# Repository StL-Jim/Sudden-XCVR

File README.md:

# Sudden-XCVR

These are the EagleCAD schematics and board files for the QRP Transceiver designed and built by Pete Julino N6QW called the Sudden Transceiver.  

I am very new to building a truly scratch built rig, so any suggestions, comments, corrections are greatly appreciated.

Read about the Sudden Scratch Built SSB Transceiver - http://www.n6qw.com/Sudden.html

I use a style of construction coined by Chuck Adams K7QO called 'Muppet Style', you can learn about this style of building from Chuck's YouTube channel

* https://www.youtube.com/watch?v=O6AmT1trO60

As I progress along I'll be adding PDF of the schematics and boards as well as the EagleCAD parts library I use.

73 - AE0BZ

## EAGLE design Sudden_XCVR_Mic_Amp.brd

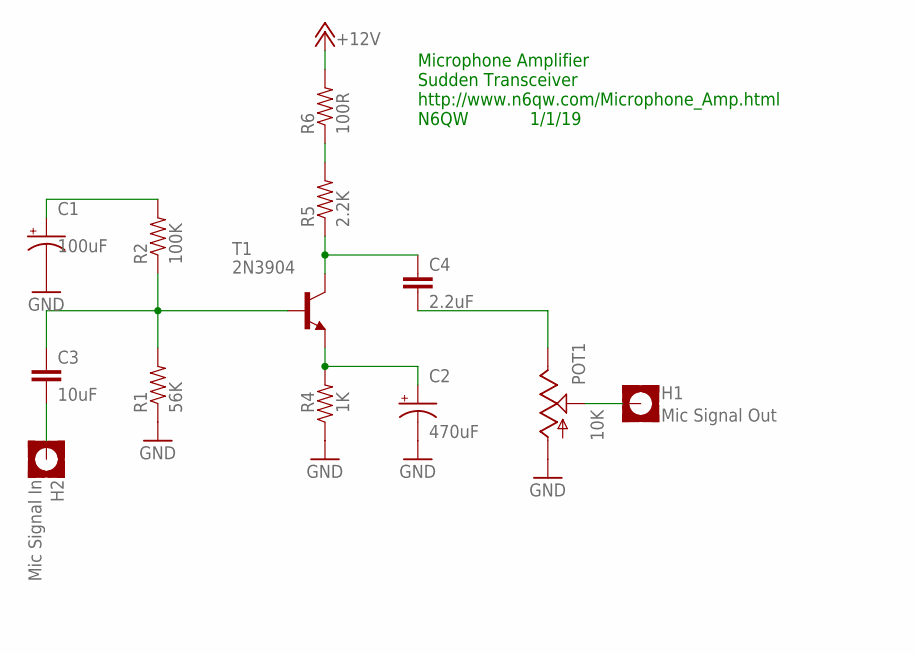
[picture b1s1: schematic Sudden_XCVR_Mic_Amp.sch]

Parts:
C1: 100uF; CAP-POLARIZED
C2: 470uF; CAP-POLARIZED
C3: 10uF; CAP-MEDIUM-MUPPET
C4: 2.2uF; CAP-MEDIUM-MUPPET
H1: Mic Signal Out; PAD-SQUARE
H2: Mic Signal In; PAD-SQUARE
P+1: +12V; POWER-IN-PAD
POT1: 10K; POT-TRIMM-4
R1: 56K; RESITOR-MUPPET
R2: 100K; RESITOR-MUPPET
R4: 1K; RESITOR-MUPPET
R5: 2.2K; RESITOR-MUPPET
R6: 100R; RESITOR-MUPPET
T1: 2N3904; TO92

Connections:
+12V: P+1.VCC, R6.P$2 (2)
GND: C1.2 (-), C2.2 (-), POT1.A, R1.P$1 (1), R4.P$1 (1)
unnamed: C4.1, R5.P$1 (1), T1.1 (C)
unnamed: C2.1 (+), R4.P$2 (2), T1.3 (E)
unnamed: C4.2, POT1.E
unnamed: C3.1, R1.P$2 (2), R2.P$1 (1), T1.2 (B)
unnamed: C1.1 (+), R2.P$2 (2)
unnamed: R5.P$2 (2), R6.P$1 (1)
unnamed: H1.PAD, POT1.S
unnamed: C3.2, H2.PAD

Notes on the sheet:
Microphone Amplifier Sudden Transceiver http://www.n6qw.com/Microphone_Amp.html N6QW 1/1/19

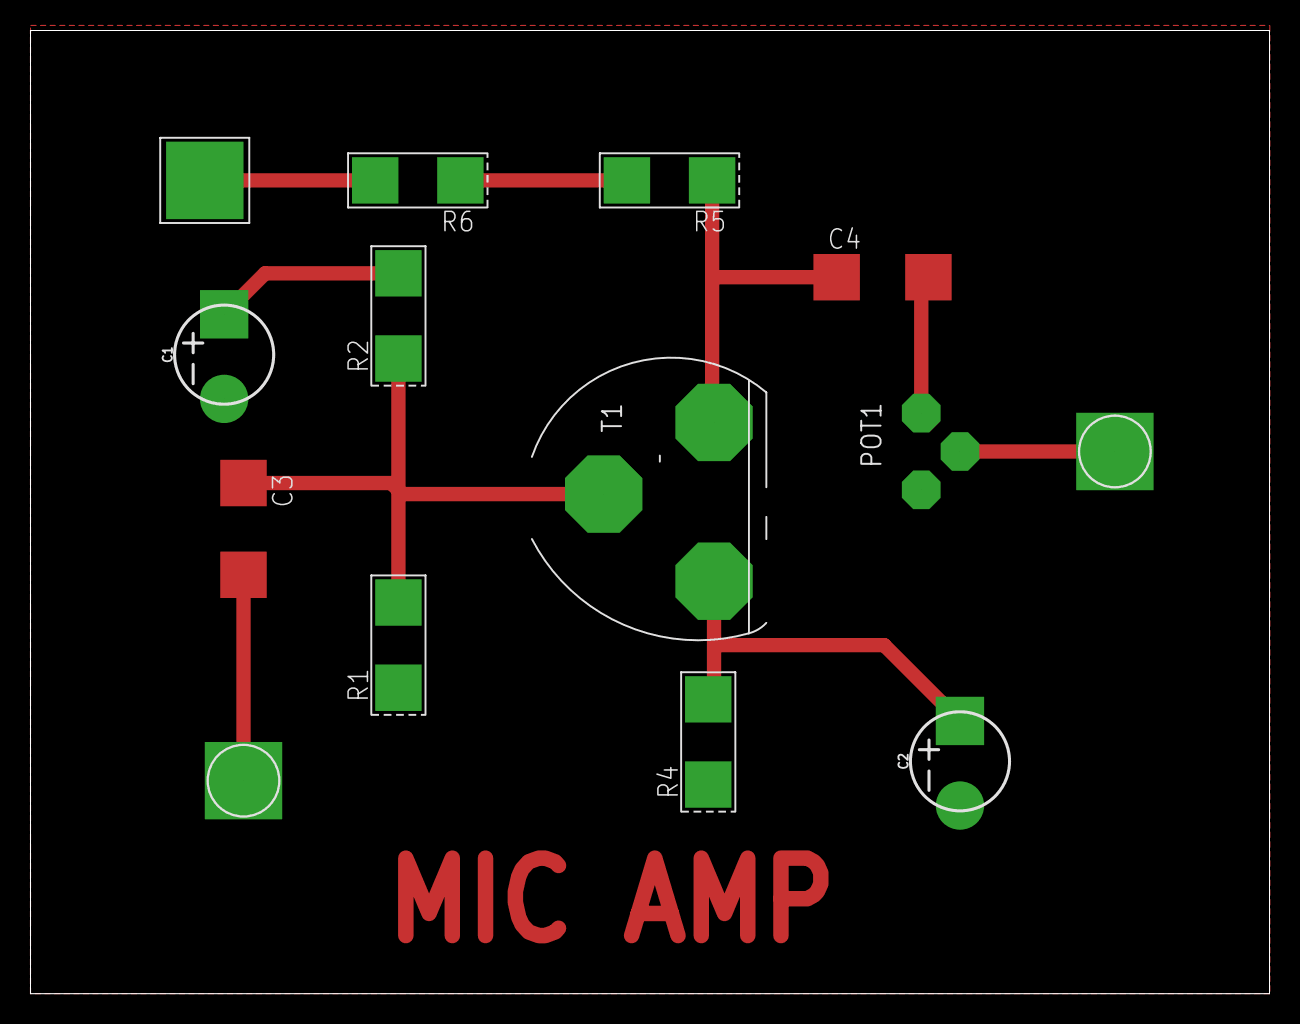
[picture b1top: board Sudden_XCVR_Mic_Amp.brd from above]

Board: 2 copper layers, 81.3 x 63.2 mm, 14 parts (1 on the bottom side), 10 nets.

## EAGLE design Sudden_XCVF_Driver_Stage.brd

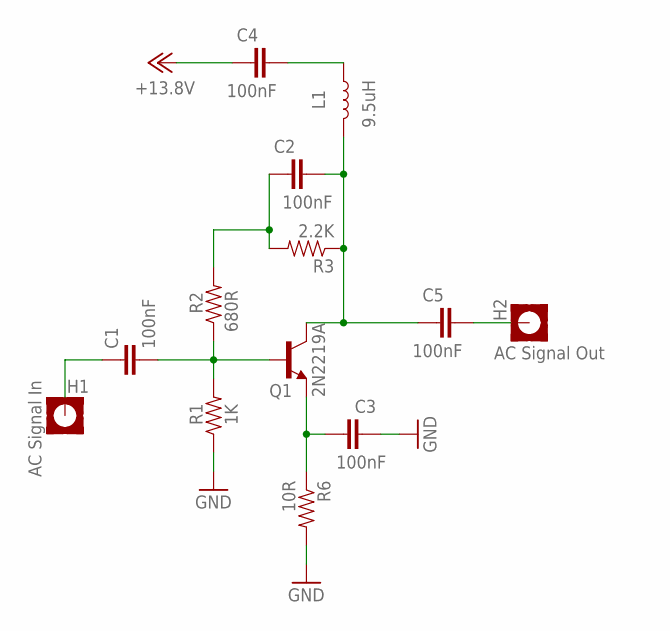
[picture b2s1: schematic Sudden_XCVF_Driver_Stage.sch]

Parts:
C1, C2, C3, C4, C5: 100nF; CAP-MEDIUM-MUPPET
H1: AC Signal In; PAD-SQUARE
H2: AC Signal Out; PAD-SQUARE
L1: 9.5uH; INDUCTOR_2.2UH
P+1: +13.8V; POWER-IN-PAD
Q1: 2N2219A; 2N2222-TO18
R1: 1K; RESITOR-MUPPET
R2: 680R; RESITOR-MUPPET
R3: 2.2K; RESITOR-MUPPET
R6: 10R; RESITOR-MUPPET

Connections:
+12V: C4.1, P+1.VCC
GND: C3.1, R1.P$1 (1), R6.P$2 (2)
unnamed: C1.2, Q1.2 (B), R1.P$2 (2), R2.P$1 (1)
unnamed: C2.2, C5.1, L1.P$2 (2), Q1.3 (C), R3.P$1 (1)
unnamed: C5.2, H2.PAD
unnamed: C2.1, R2.P$2 (2), R3.P$2 (2)
unnamed: C1.1, H1.PAD
unnamed: C4.2, L1.P$1 (1)
unnamed: C3.2, Q1.1 (E), R6.P$1 (1)

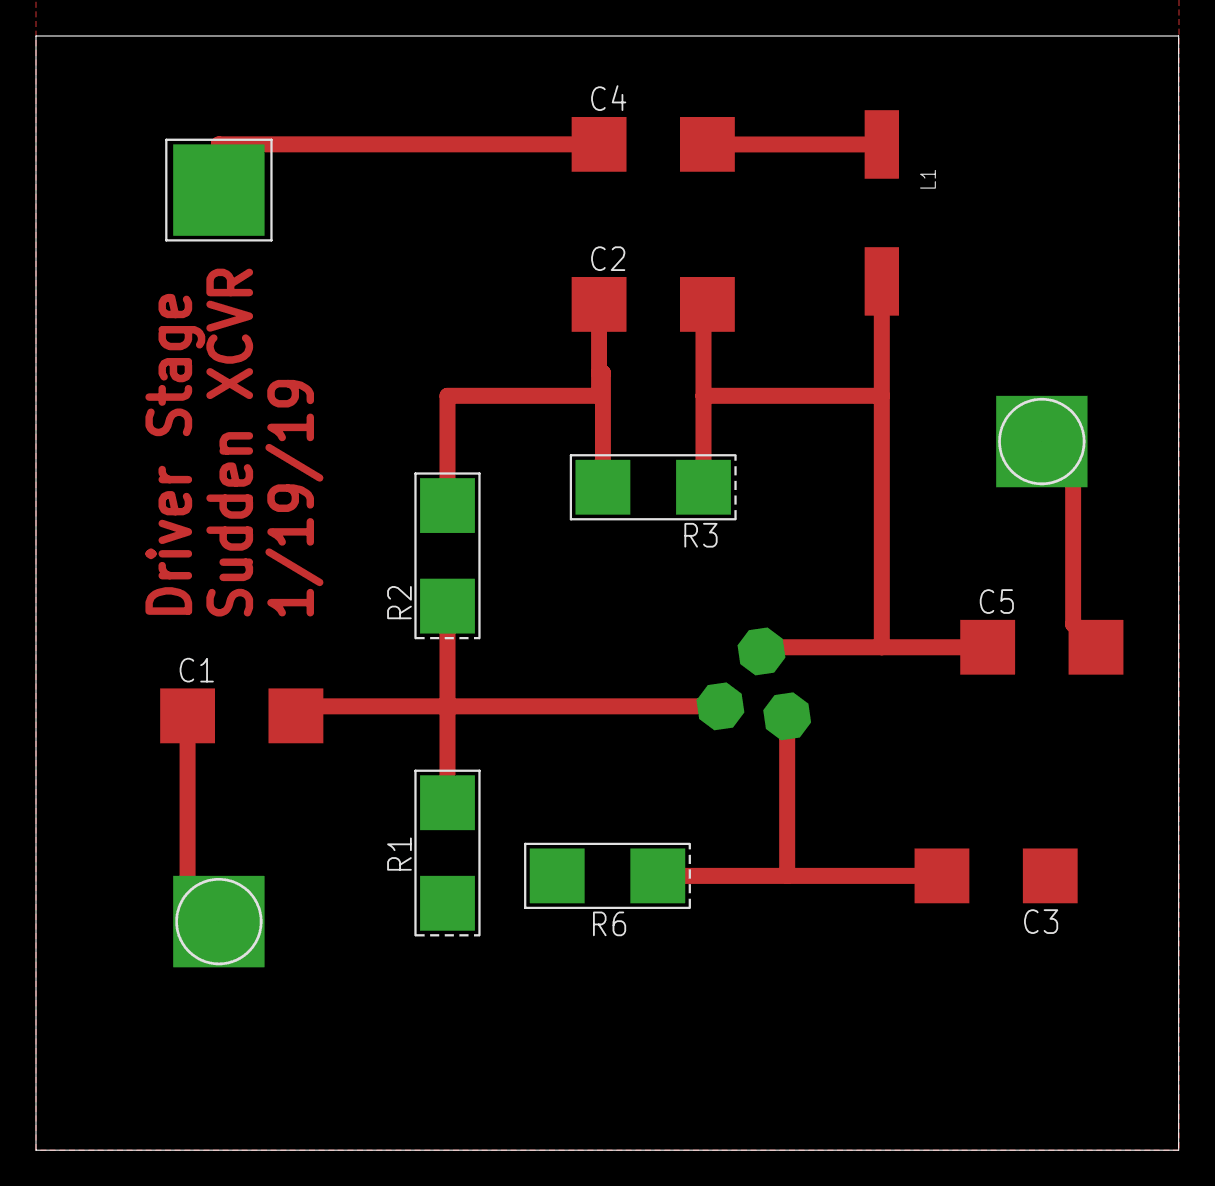
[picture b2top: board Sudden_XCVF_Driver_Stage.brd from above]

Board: 2 copper layers, 63.5 x 61.9 mm, 14 parts (1 on the bottom side), 9 nets.

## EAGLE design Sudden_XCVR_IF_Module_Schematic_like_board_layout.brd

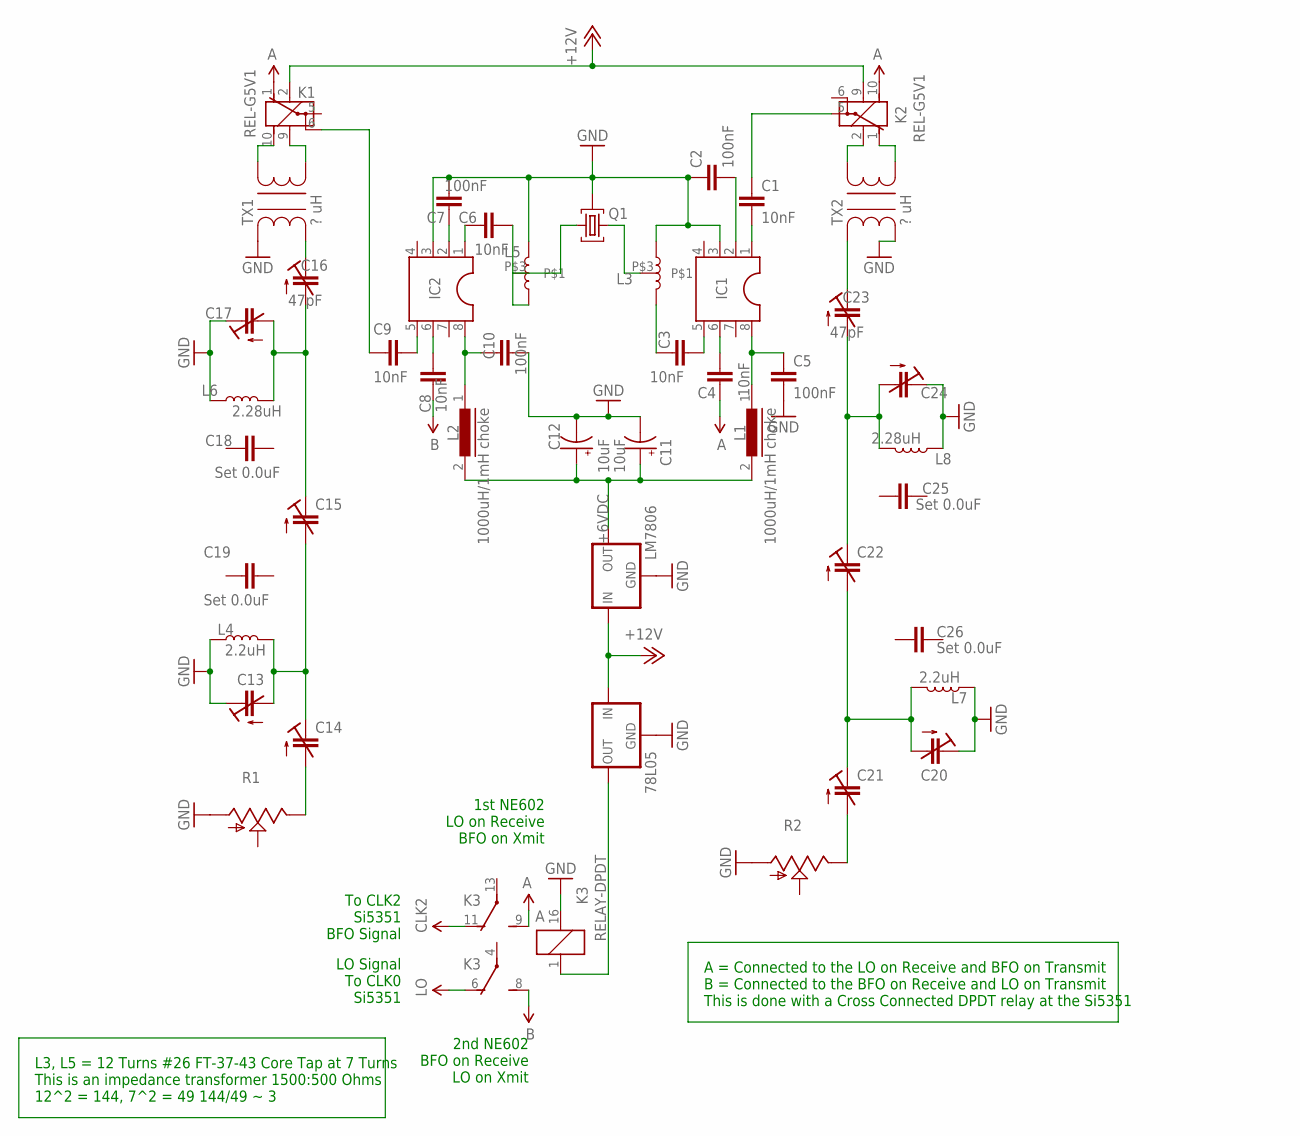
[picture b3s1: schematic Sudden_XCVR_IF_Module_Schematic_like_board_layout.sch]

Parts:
78L05: 78XXL
A, A1, A2: A; POWER-IN-PAD
B: B; POWER-IN-PAD
C1, C3, C4, C6, C8, C9: 10nF; CAP-MEDIUM-MUPPET
C2, C5, C7, C10: 100nF; CAP-MEDIUM-MUPPET
C11, C12: 10uF; CAP-POLARIZED
C13, C14, C15, C17, C20, C21, C22, C24: CAP-TRIMM3008; CAP-TRIMM
C16, C23: 47pF; CAP-TRIMM
C18, C19, C25, C26: Set 0.0uF; CAP-MEDIUM-MUPPET
CLK0: LO; POWER-IN-PAD
CLK1: A; POWER-IN-PAD
CLK2: CLK2; POWER-IN-PAD
IC1, IC2: DUAL-INLINE-8DIL08-2; DIL08
K1, K2: REL-G5V1; G5V1
K3: RELAY-DPDT; G5V-2
L1, L2: 1000uH/1mH choke; MOLDED-CHOKE
L3: INDUCTOR-TAPPED; INDUCTOR_TAPPED
L4, L7: 2.2uH; INDUCTOR_2.2UH
L5: INDUCTOR-TAPPED; INDUCTOR_TAPPED_MIRRORED
L6, L8: 2.28uH; INDUCTOR_2.2UH
LM7806: 78XXL
P+1, P+2: +12V; POWER-IN-PAD
Q1: CRYSTAL-FILTER
R1, R2: POTENTIOMETER-TRIMCT6; POT-TRIMM-4
SUPPLY1: B; POWER-IN-PAD
TX1, TX2: ? uH; TRANSFORMER_TWO_WIRE

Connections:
3.3V: A1.VCC, A2.VCC, B.VCC, C8.1, K1.1 (O), K2.10 (S), K3.8 (S), SUPPLY1.VCC
+6VDC: C11.1 (+), C12.1 (+), L1.2, L2.2, LM7806.OUT
+12V: 78L05.IN, K1.2 (1), K2.9 (2), LM7806.IN, P+1.VCC, P+2.VCC
A: A.VCC, C4.1, CLK0.VCC, CLK1.VCC, K3.6 (O), K3.9 (S)
BFO: CLK2.VCC, K3.11 (O)
GND: 78L05.GND, C2.1, C5.2, C7.1, C10.2, C11.2 (-), C12.2 (-), C13.+ (E), C17.+ (E), C20.+ (E), C24.+ (E), IC1.3, IC2.3, K3.16 (2), L3.P$2 (2), L4.P$1 (1), L5.P$1 (1), L6.P$1 (1), L7.P$1 (1), L8.P$1 (1), LM7806.GND, Q1.3, R1.A, R2.A, TX1.C1B (2), TX2.C1A (1)
unnamed: C5.1, IC1.8, L1.1
unnamed: C4.2, IC1.6
unnamed: C3.2, IC1.5
unnamed: L5.P$3, Q1.1
unnamed: C1.2, IC1.1
unnamed: 78L05.OUT, K3.1
unnamed: C2.2, IC1.2
unnamed: C16.+ (E), TX1.C1A (1)
unnamed: C10.1, IC2.8, L2.1
unnamed: C8.2, IC2.6
unnamed: C9.2, IC2.5
unnamed: C6.2, IC2.1
unnamed: C6.1, L5.P$2 (2)
unnamed: C7.2, IC2.2
unnamed: L3.P$3, Q1.2
unnamed: C3.1, L3.P$1 (1)
unnamed: C1.1, K2.5
unnamed: C9.1, K1.6
unnamed: C15.+ (E), C16.- (A), C17.- (A), L6.P$2 (2)
unnamed: C14.- (A), R1.E
unnamed: C13.- (A), C14.+ (E), C15.- (A), L4.P$2 (2)
unnamed: C23.+ (E), TX2.C1B (2)
unnamed: C22.+ (E), C23.- (A), C24.- (A), L8.P$2 (2)
unnamed: C20.- (A), C21.+ (E), C22.- (A), L7.P$2 (2)
unnamed: C21.- (A), R2.E
unnamed: K1.9 (2), TX1.C2A (5)
unnamed: K1.10 (S), TX1.C2B (6)
unnamed: K2.2 (1), TX2.C2B (6)
unnamed: K2.1 (O), TX2.C2A (5)

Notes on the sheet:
L3, L5 = 12 Turns #26 FT-37-43 Core Tap at 7 Turns This is an impedance transformer 1500:500 Ohms 12^2 = 144, 7^2 = 49 144/49 ~ 3
A = Connected to the LO on Receive and BFO on Transmit B = Connected to the BFO on Receive and LO on Transmit This is done with a Cross Connected DPDT relay at the Si5351
1st NE602 LO on Receive BFO on Xmit
2nd NE602 BFO on Receive LO on Xmit
LO Signal To CLK0 Si5351
To CLK2 Si5351 BFO Signal

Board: 2 copper layers, 56 parts (0 on the bottom side), 35 nets, no tracks yet.

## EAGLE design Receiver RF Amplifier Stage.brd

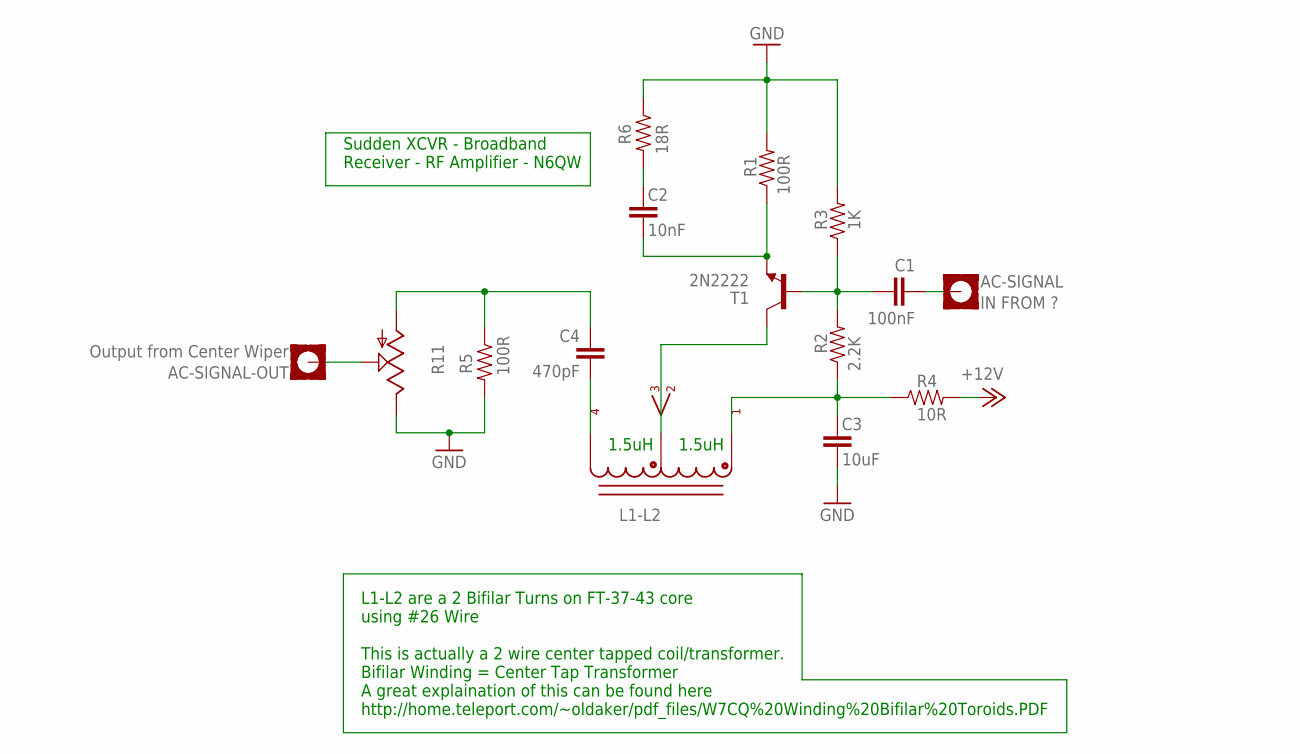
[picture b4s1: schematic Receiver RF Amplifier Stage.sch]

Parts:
AC-SIGNAL: IN FROM ?; PAD-SQUARE
AC-SIGNAL-OUT: Output from Center Wiper; PAD-SQUARE
C1: 100nF; CAP-MEDIUM-MUPPET
C2: 10nF; CAP-MEDIUM-MUPPET
C3: 10uF; CAP-MEDIUM-MUPPET
C4: 470pF; CAP-MEDIUM-MUPPET
L1-L2: T37-43_BIFILAR_TORIODBIFILAR-COIL/TRANSFORMER; T37-43_BIFILAR_TOROID
P+1: +12V; POWER-IN-PAD
R1, R5: 100R; RESITOR-MUPPET
R2: 2.2K; RESITOR-MUPPET
R3: 1K; RESITOR-MUPPET
R4: 10R; RESITOR-MUPPET
R6: 18R; RESITOR-MUPPET
R11: POTENTIOMETER-TRIMCT6; POT-TRIMM-4
T1: 2N2222; 2N2222-TO18

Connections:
+12V: P+1.VCC, R4.P$2 (2)
GND: C3.1, R1.P$2 (2), R3.P$2 (2), R5.P$2 (2), R6.P$1 (1), R11.E
unnamed: C1.1, R2.P$2 (2), R3.P$1 (1), T1.2 (B)
unnamed: AC-SIGNAL-OUT.PAD, R11.S
unnamed: C2.2, R6.P$2 (2)
unnamed: L1-L2.C2A, T1.3 (C)
unnamed: C4.1, L1-L2.C3A
unnamed: C3.2, L1-L2.C1A, R2.P$1 (1), R4.P$1 (1)
unnamed: C4.2, R5.P$1 (1), R11.A
unnamed: AC-SIGNAL.PAD, C1.2
unnamed: C2.1, R1.P$1 (1), T1.1 (E)

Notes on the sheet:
Sudden XCVR - Broadband Receiver - RF Amplifier - N6QW
L1-L2 are a 2 Bifilar Turns on FT-37-43 core using #26 Wire This is actually a 2 wire center tapped coil/transformer. Bifilar Winding = Center Tap Transformer A great explaination of this can be found here http://home.teleport.com/~oldaker/pdf_files/W7CQ%20Winding%20Bifilar%20Toroids.PDF
1.5uH

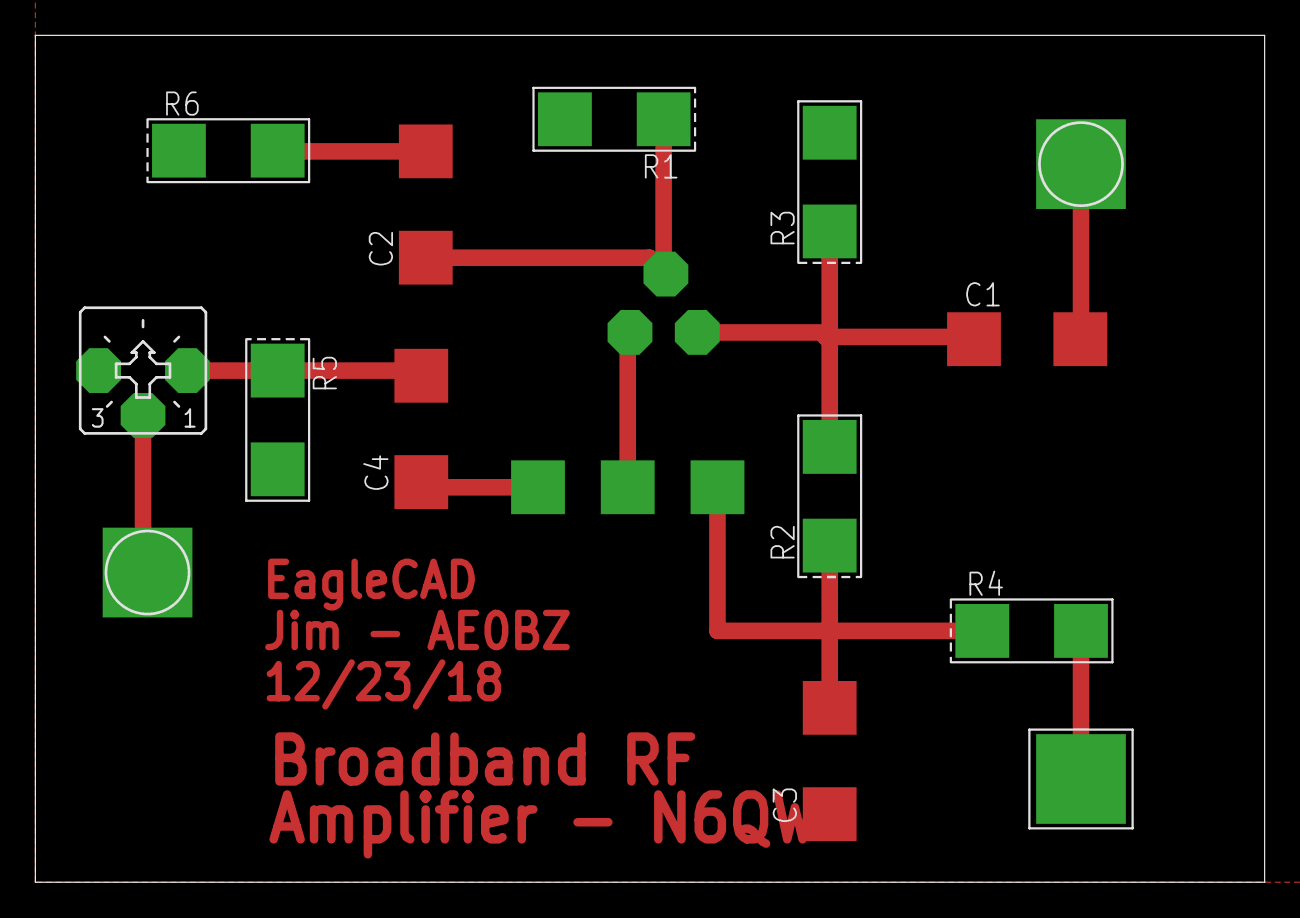
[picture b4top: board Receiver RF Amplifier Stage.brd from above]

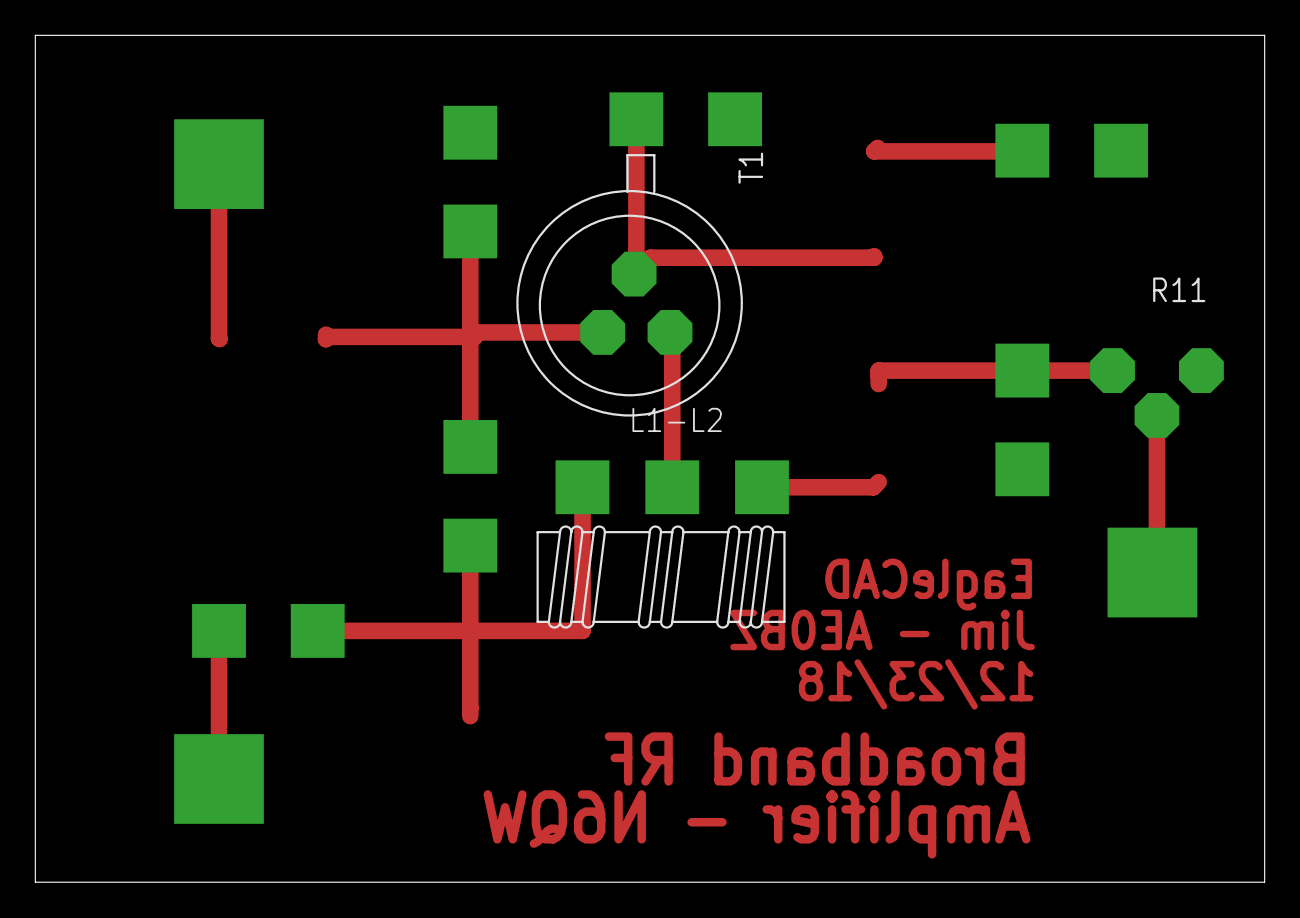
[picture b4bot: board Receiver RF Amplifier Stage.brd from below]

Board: 2 copper layers, 69.6 x 47.9 mm, 16 parts (2 on the bottom side), 11 nets.

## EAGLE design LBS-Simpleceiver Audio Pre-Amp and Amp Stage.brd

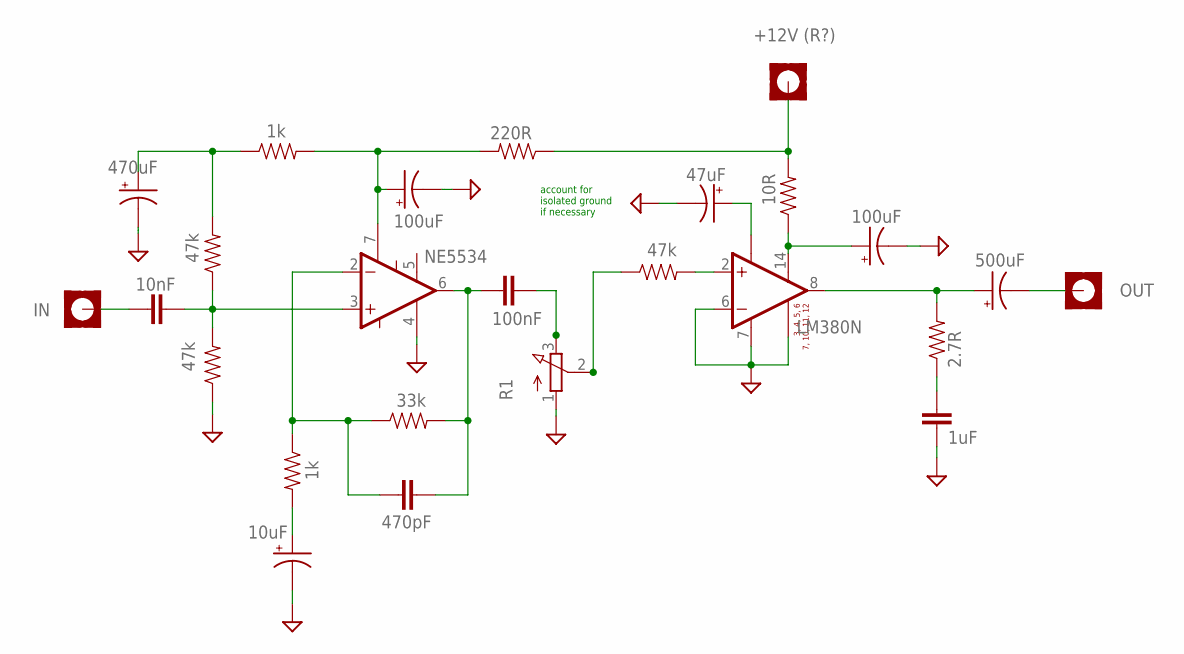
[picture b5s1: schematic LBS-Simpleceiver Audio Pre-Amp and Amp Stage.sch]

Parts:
C1: 470uF; CAP-POLARIZED
C2, C6: 100uF; CAP-POLARIZED
C3: 500uF; CAP-POLARIZED
C4: 47uF; CAP-POLARIZED
C5: 10uF; CAP-POLARIZED
C7: 10nF; CAP-MEDIUM-MUPPET
C8: 100nF; CAP-MEDIUM-MUPPET
C9: 1uF; CAP-MEDIUM-MUPPET
C10: 470pF; CAP-MEDIUM-MUPPET
H1: IN; PAD-SQUARE
H2: OUT; PAD-SQUARE
H3: +12V (R?); PAD-SQUARE
IC1: NE5534; DIL08
R1: POTENTIOMETER
R2, R3: 47k; RESITOR-MUPPET
R4: 1k; RESITOR-MUPPET
R5: 33k; RESITOR-MUPPET
R8: 220R; RESITOR-MUPPET
R9: 2.7R; RESITOR-MUPPET
U1: LM380N; DIL14
U$4: 1k; RESITOR-MUPPET
U$6: 47k; RESITOR-MUPPET
U$7: 10R; RESITOR-MUPPET

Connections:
GND: C1.2 (-), C2.2 (-), C4.2 (-), C5.2 (-), C6.2 (-), C9.2, IC1.4 (VCC-GND), R1.1 (A), R3.P$1 (1), U1.3 (GND), U1.4 (GND), U1.5 (GND), U1.6 (-IN), U1.7 (GND1), U1.10 (GND), U1.11 (GND), U1.12 (GND)
unnamed: C7.1, H1.PAD
unnamed: C7.2, IC1.3 (+IN), R2.P$1 (1), R3.P$2 (2)
unnamed: C1.1 (+), R2.P$2 (2), R4.P$1 (1)
unnamed: C6.1 (+), IC1.7 (VCC+), R4.P$2 (2), R8.P$2 (2)
unnamed: C8.2, C10.1, IC1.6 (OUT), R5.P$2 (2)
unnamed: C10.2, IC1.2 (-IN), R5.P$1 (1), U$4.P$1 (1)
unnamed: C5.1 (+), U$4.P$2 (2)
unnamed: C8.1, R1.3 (E)
unnamed: R1.2 (S), U$6.P$1 (1)
unnamed: U1.2 (+IN), U$6.P$2 (2)
unnamed: C2.1 (+), U1.14 (V-SIG), U$7.P$1 (1)
unnamed: H3.PAD, R8.P$1 (1), U$7.P$2 (2)
unnamed: C3.1 (+), R9.P$2 (2), U1.8 (GAIN)
unnamed: C9.1, R9.P$1 (1)
unnamed: C4.1 (+), U1.1 (BYPASS)
unnamed: C3.2 (-), H2.PAD

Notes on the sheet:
account for isolated ground if necessary

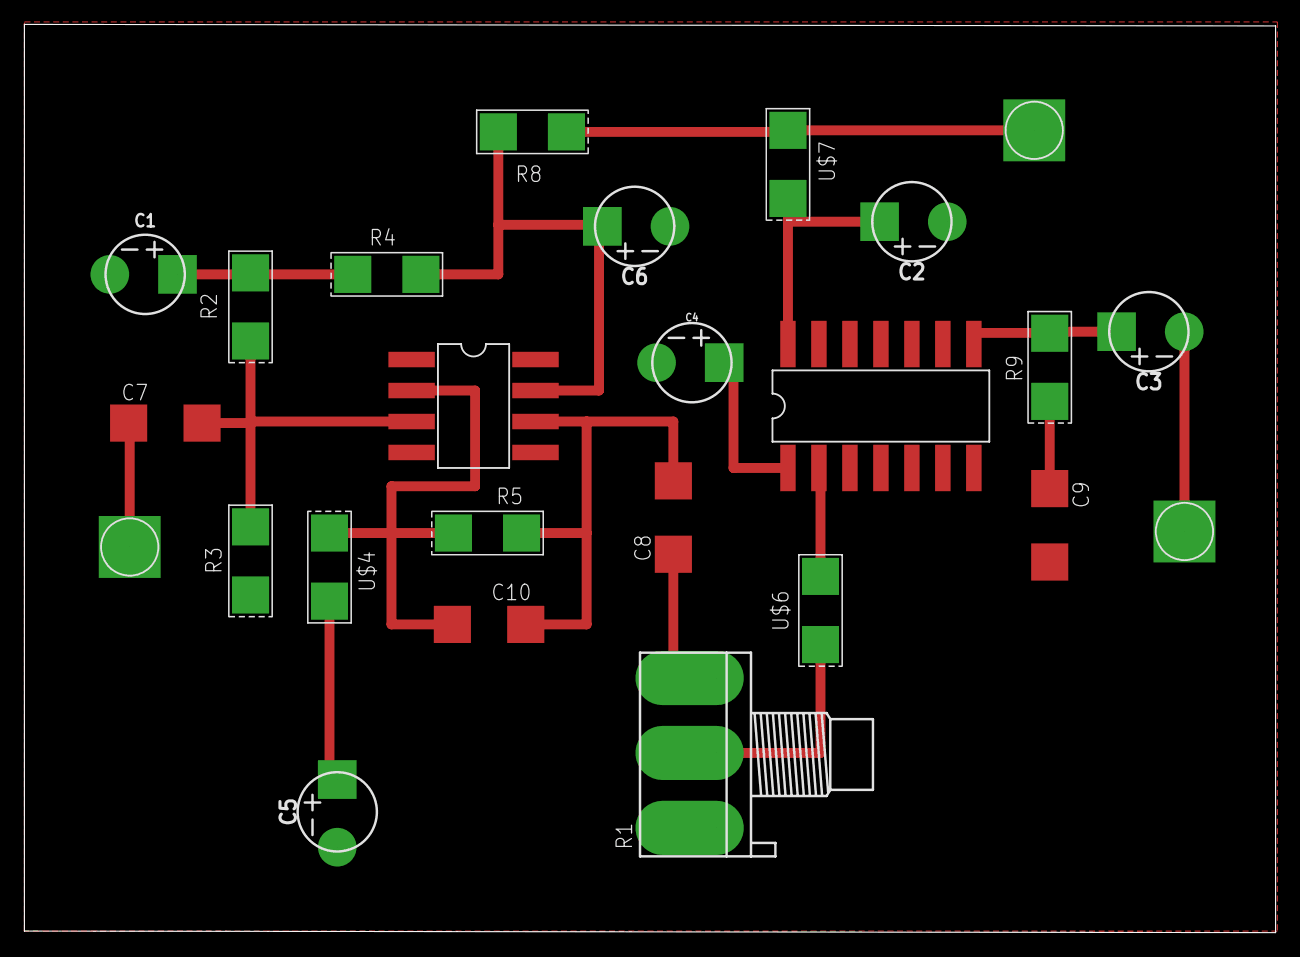
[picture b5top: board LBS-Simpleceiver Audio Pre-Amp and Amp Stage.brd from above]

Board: 2 copper layers, 102.6 x 74.5 mm, 25 parts (0 on the bottom side), 17 nets.

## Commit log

2018-12-15 inital commit
2018-12-15 Initial commit of Sudden XCVR On branch master Changes to be committed: new file: LBS-Simpleceiver Audio Pre-Amp and Amp Stage.b#1 new file: LBS-Simpleceiver Audio Pre-Amp and Amp Stage.b#2 new file: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
2018-12-15 Update to README.md with a bit more information
2018-12-15 Adding some images as well as updates
    Adding some images as well as updates to the Receiver RF Amplifier Stage
2018-12-23 Updated schematic to have a bifilar winding
    Updated schematic to have a bifilar winding or center tapped
    transformer.
    Also starting to work on the board.
    On branch master
    Your branch is up-to-date with 'origin/master'.
    Changes to be committed:
2018-12-31 Lots of changes.
    Recreated the IF Schema and a new board to look like the photo
    On branch master
    Changes to be committed:
    modified: Receiver RF Amplifier Stage.b#1
    modified: Receiver RF Amplifier Stage.b#2
    modified: Receiver RF Amplifier Stage.b#3
2019-01-02 Added Pre-Driver and Mic Amp
    Added Pre-Driver and Mic Amp
    On branch master
    Changes to be committed:
    new file: Sudden_XCVF_Transmit_Pre-Driver_Stage.s#1
    new file: Sudden_XCVF_Transmit_Pre-Driver_Stage.sch
    new file: Sudden_XCVR_Mic_Amp.b#1
2019-01-06 Added additional schematics and board layout
    Added additional schmentics and board layout for Driver stage and a new IF schematic and board
2019-01-19 Updated the IF module - mainly board layout
    Updated the IF module - mainly board layout
2019-01-19 Still needed traces for Mic Amp board
    On branch master
    Changes to be committed:
    modified: Sudden_XCVF_Driver_Stage.b#1
    modified: Sudden_XCVF_Driver_Stage.b#2
    modified: Sudden_XCVF_Driver_Stage.b#3
    new file: Sudden_XCVF_Driver_Stage.b#4
2019-01-21 On branch master Changes to be committed: modified: Sudden_XCVF_Driver_Stage.b#1 modified: Sudden_XCVF_Driver_Stage.b#2 modified: Sudden_XCVF_Driver_Stage.b#3 modified: Sudden_XCVF_Driver_Stage.b#4 m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
2019-01-21 Added Mic Amp
    Added Mic Amp, not sure this will conflict with previous commit
    On branch master
    Changes to be committed:
    modified: Sudden_XCVR_Mic_Amp.b#1
    modified: Sudden_XCVR_Mic_Amp.b#2
    modified: Sudden_XCVR_Mic_Amp.b#3
2019-01-26 Not sure what changed here
    On branch master
    Changes to be committed:
    modified: eagle.epf
2019-03-17 Place to put DC Circuits Class Labs
    Place to put DC Circuits Class Labs
    On branch master
    Changes to be committed:
    new file: DC Circuits Class/BreadBoard_Simple_Parallel_Resistive_Circuit.s#1
    new file: DC Circuits Class/BreadBoard_Simple_Parallel_Resistive_Circuit.s#2
    new file: DC Circuits Class/BreadBoard_Simple_Parallel_Resistive_Circuit.sch
2019-03-17 Hope for no collision On branch master Changes to be committed: modified: eagle.epf
2019-03-17 This is going to cause a merge conflict
    Changes to be committed:
    modified: eagle.epf
